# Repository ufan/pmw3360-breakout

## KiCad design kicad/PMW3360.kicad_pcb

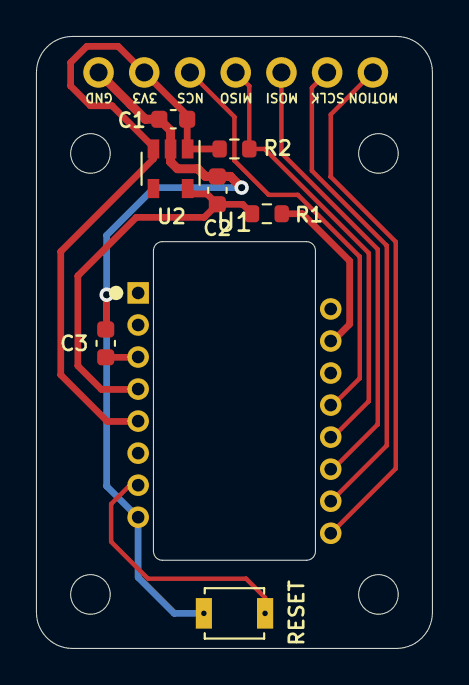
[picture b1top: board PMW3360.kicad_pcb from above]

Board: 2 copper layers, 22.0 x 34.0 mm, 9 parts (0 on the bottom side), 11 nets.

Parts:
C1: 0.1u; C_0603_1608Metric
C2: 1u; C_0603_1608Metric
C3: 4.7u; C_0603_1608Metric
J1: Conn_01x07; PinHeader_1x07_P2.54mm_Vertical
R1: 39; R_0603_1608Metric
R2: 10k; R_0603_1608Metric
U1: PMW3360
U2: TCR2EF19; SOT-23-5
sw_reset1: SW_RESET-kbd; SW_B3U-1000P_reversible

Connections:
+1V8: C2.1, R1.1, U1.4 (VDD), U2.5 (OUT)
+3V3: C1.2, J1.2, R2.1, U1.5 (VDDIO), U2.1 (IN), U2.3 (EN)
GND: C1.1, C2.2, C3.2, J1.1, U1.8 (GND), U2.2 (GND), sw_reset1.1
MISO: J1.4, R2.2, U1.12 (MISO)
MOSI: J1.5, U1.11 (MOSI)
MOTION: J1.7, U1.9 (MOTION)
NCS: J1.3, U1.13 (NCS)
unnamed: C3.1, U1.3 (VDDPIX)
unnamed: R1.2, U1.15 (LED_P)
RESET: U1.7 (NRESET), sw_reset1.2
SCLK: J1.6, U1.10 (SCLK)

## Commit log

2022-07-01 add a reset button
2022-07-01 add 3d model of pmw3360
2022-07-30 add ibom file
2022-08-01 add optical center circle
2022-08-02 [modify] lens outline based on manual, adding slight tolerance
